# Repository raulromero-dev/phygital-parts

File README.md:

# Phygital Parts

Live at [phygitalstudio.app](https://phygitalstudio.app/).

A standalone hardware workbench for discovering components, visualizing their
fit, planning real cables, and deciding what to buy. Start with a description,
a reference photo plus a prompt, or public links to a project or product.

The homepage offers six **prebuilt starters** without an API key: makeup cyberdeck,
thermal camera, air monitor, wearable haptics, smartwatch and smart ring.
Each opens a populated 3D layout with proposed connections, sourcing links
and review notes. Original Phygital compact, bench and wide layouts remain
available through their direct project URLs.

Each starter has its own URL and browser-storage namespace:
`/examples/thermal-camera`, `/examples/air-monitor`, `/examples/wearable-haptics`,
`/examples/smartwatch`, `/examples/smart-ring`, `/examples/makeup-cyberdeck`, and
`/projects/phygital?layout=compact` (also `bench` or `wide`). Autosaves,
snapshots and chat histories stay separate. The Phygital route retains the
original project inventory, notes and source context, with links to its firmware
repository and original workbench. Existing root-page projects remain available.

### Saving and returning

**My projects** lists account projects and older browser saves. Sign in with
Google to return from any device. New prompted builds save to your account while
signed in. Use **Projects → Save to account** to copy an existing browser project;
its original stays local. Account edits and the last 40 chat messages autosave.

Without sign-in, projects remain in this browser. **Save a copy** and **Import
project** create independent projects; they never replace the source. Copies and
imports go to your account when signed in. The sidebar name is editable, and
named layouts keep independent parts, placements and cables within one project.
Use the layout selector and compare button to switch, duplicate, rename or remove
alternatives. They autosave to the account or browser with the project; older
snapshots remain available under **Layouts → Older snapshots & examples**.

**Export → Project file** creates a portable JSON backup of the assembly, cables,
custom parts, all layout alternatives, notes and decisions (no chat or keys). Clearing site data removes
browser copies, not account copies. A cloud URL requires its owner's sign-in;
it does not make the project public. Save failures and conflicts are visible;
conflicts preserve your draft and offer Save a copy instead of overwriting.

See [account setup](docs/ACCOUNTS.md) to configure a fork and run database checks.

The smart ring reuses SenseRing's four original CAD meshes: sensor board,
curved battery, inner shell and outer shell. It is a custom fabrication reference,
not a plug-in kit. Battery availability and curved clearances need review.
Editable CAD, PCB files, source meshes, conversion script and GPL-3.0 license
are available at `/reference/sense-ring/source.zip`.

The smartwatch uses a Seeed
XIAO ESP32-S3, Round Display, included antenna allowance and LiPol LPR553535
round 600 mAh battery candidate. It maps the 14 direct header contacts and antenna coax.
The battery remains unconnected: its 300 mA charge limit is below the board’s
approximately 485 mA setting, and its PHR-2 plug requires an adapter. LiPol lists
a five-piece minimum for stocked samples; confirm availability and pricing. Published
PCB data and the existing XIAO CAD are reused; thickness, antenna geometry and
the proposed enclosure are estimates. Inspect each part for manufacturer purchase links and pinouts; the project
includes open-source examples and a printable case reference.

This repository is independent of the original Phygital sensor firmware. It
contains the product experience and a reusable reference-model library, not the
surveillance device's firmware or detection rules.

The makeup cyberdeck pairs M5Stack's current Cardputer-Adv with an original
blush compact cradle, hinged lid and mirror insert. Manufacturer STL is reused
under MIT; the case is an open-position fit concept. Hinge collisions remain
visible for review. The controller, keyboard, screen and 1500 mAh battery are
integrated, so the starter has no external conductors. See **Pins & internals**
for the internal map and Grove expansion contacts. Source and license bundle:
`/reference/makeup-cyberdeck/source.zip`.

Select a component and ask Codex, for example: “Find an alternative near 02134
from Amazon or Micro Center that I can get within two days.” You can also use
Find parts → codex. Include a city/ZIP and deadline; no precise address is needed.
Codex can search the web, compare the exact SKU and connection requirements, and
show retailer links with dated availability evidence. Generic stock is kept
separate from arrival dates. Missing evidence stays unverified; results older
than a day ask you to recheck. **Check fit & add…** researches a candidate for
review; it never automatically swaps your existing component or purchases it.
Shopping cards stay in private account/browser chat, excluded from shared layouts.

Find parts cards show names, dimensions and purchasing actions first. Interface
text and research descriptions are available in collapsed details. Research
and link forms use brief labels instead of introductory subtitles. The homepage
accepts part links directly in the main prompt, without a separate links field.
A first prompt opens its own project URL with the floating Codex window open.
Validated draft parts appear progressively, followed by source CAD or an
image-derived model. Codex shows real progress, elapsed time and Stop.
Canceled or interrupted builds retain their draft parts.
Stages come from provider events; no percentage is invented. Loading shows quiet
action text. The optional Cable Hop game opens from Codex while work continues
in the background.

## For agents and contributors

Start with [AGENTS.md](AGENTS.md), [architecture](docs/ARCHITECTURE.md),
[adding parts](docs/ADDING_PARTS.md), and [CONTRIBUTING.md](CONTRIBUTING.md).
These explain the product context, model provenance, coordinates, connection
rules, code boundaries, local setup and validation workflows.

The reusable [Phygital skill](skills/phygital/SKILL.md) helps agents discover parts,
compare fit and plan connections. Its name and description support automatic
skill discovery; invoke it explicitly as **`$phygital`**. Install from a checkout:

```sh
mkdir -p ~/.codex/skills
cp -R skills/phygital ~/.codex/skills/
```

Start a new Codex session to refresh skill discovery. The same package is available
as [a downloadable skill](https://phygitalstudio.app/skills/phygital.zip) or
[readable instructions](https://phygitalstudio.app/skills/phygital.md). Other agents
can load `SKILL.md` with their own skill mechanism. To update the distribution
from source, run `npm run skill:package` (Python 3). This is a repository-distributed
skill; it does not require a hosted tool server.

Original application code, documentation and the skill are MIT licensed.
Third-party CAD, derived assets, fonts and icons retain their existing attribution
and terms; the application license does not relicense those files.

## Use

1. Describe a project on the homepage, or choose a prebuilt starter.
2. Connect your own OpenAI API key to use **GPT-6 Astra**. Research uses the
   Responses API, image input, web search and structured output.
3. Review the proposed parts, sources, unknowns and conductors. Select the parts
   to add. An AI response never silently replaces the current assembly.
4. Use **Find parts** to search the local library, work with codex, paste a product URL,
   or add a component manually. Purchase links are prominent on cards and in
   the part inspector. Search-result links are labeled as searches; stock and
   prices are not promised.
5. Arrange parts in 3D, adjust dimensions, set enclosure bounds, inspect fit
   checks, and map individual contacts in **Connections**. Export JSON to move a
   project between browsers, GLB for Blender, or CSV for the cable plan.
6. Open **codex** for a floating, expandable chat. Select a part to attach
   its context, then request movement, rotation, corrected dimensions, enclosure
   changes or review notes. Review each proposal and choose **Apply changes**;
   the edit is undoable. Proposals are rejected if the assembly has changed
   since the request. Codex can also add or duplicate catalog/existing parts and
   map their contacts. Ask for alternatives to receive up to four independent
   layout proposals at once. **Save layouts** keeps the original active; use
   **Compare layouts** to open an option. A project holds up to eight layouts.

The interface supports light/dark mode and Color/Mono component rendering.
An outline board logo, a one-turn entrance animation and very faint circuit
traces decorate the homepage in both themes; reduced-motion preferences disable
animations. Controls use modestly rounded corners. On mobile, a compact project
menu groups key connection, theme, layouts and export.
Custom builds require a typed description; there is no Start empty shortcut.
All starters load locally without an AI call. The air monitor reuses
Sensirion sensor CAD and Seeed PCB data; its USB-C supply, firmware, ventilation
and peak-current budget need review. Haptics use four separate multiplexer
channels with the existing power-budget checks.
Known exact parts reuse the existing CAD/model library. Other parts first try
source GLB, STL or STEP (up to 2.8 MB); otherwise Astra reads a product image
and creates a bounded visual approximation. Missing sources keep
clearly labeled, dimensioned parametric envelopes. Research suggestions and pinouts need review.

## Local development

Node 22+ and npm are recommended.

```sh
npm ci
npm run dev
```

Open the printed local URL (default `http://127.0.0.1:5179`). The local server
runs Vite and the same `/api/research`, `/api/adjust`, `/api/model` and `/api/assets` handlers used in production.
`npm run dev:ui` is frontend-only; use the normal dev command to exercise either API.

```sh
npm test
npm run build
```

## API keys and data

- Each visitor brings their own OpenAI API key. There is no owner-funded key or
  shared spending pool. OpenAI bills the visitor's API project.
- Keys remain in JavaScript memory for that tab. They are not stored in
  localStorage, project files, snapshots, URLs, analytics or application logs.
  Reload or **Disconnect** removes the in-memory key.
- A research or adjustment request sends the key over HTTPS to this app's server, which relays
  it only to `https://api.openai.com/v1/responses`. This is a server-mediated
  integration, not a claim that the app server never sees the key.
- Prompts, supplied links, the chosen image and relevant assembly details are
  sent to OpenAI when research is requested. Adjustments send assembly details,
  selected-part context and the last eight chat messages. Requests set `store: false`; this
  does not override OpenAI's account-level retention or abuse-monitoring policy.
- Browser projects and their last 40 chat messages stay local. Account projects
  and chat sync to Supabase under the signed-in owner, with account-scoped local backups. Pending proposals are not restored
  after reload. Chat history is anchored above the composer with newest messages
  at the bottom. Images and credentials are not saved in projects or chat history.
- Supports one PNG/JPG/WebP up to 2 MB, five public links, 20 returned parts,
  60 assembled parts and 40 custom parts. Research has a 240-second upstream
  timeout, bounded model output/tool calls, and cancellation in the UI.
- The server never fetches arbitrary supplied URLs itself. OpenAI's web search
  reads public sources; private repositories and login-only pages are not
  automatically accessible. Errors, refusal and incomplete output never add parts.

## Analytics

Vercel Web Analytics is enabled for the hosted project. Production builds use
`@vercel/analytics` for standard page views; development builds do not inject it.
No custom events include prompts, project contents, images, keys or chat messages.
Forks must enable Web Analytics in their own Vercel project before deploying.

## Deployment

The Vercel project is `phygital-parts`, separate from the original studio.

```sh
vercel link # select your own project when deploying a fork
vercel deploy --prod
```

Vercel builds `dist/` and deploys the `api/` handlers as Node functions. No API key
or database environment variable is required. Function duration is configured
for up to 300 seconds; the hosting plan must support it. Public access is an
intentional product setting. Custom domain registration and payments are not
part of this repository.

## Structure

- `src/product.js`, `product.css`: prompt-first home, key connection, finder,
  progressive project builds and reviewed part additions.
- `src/product-data.js`: safe supplier links, blank projects, duplicate parts,
  placement suggestions and applying research proposals.
- `src/main.js`: workspace, component inspector, wiring editor, notes and export.
- `src/routes.js`, `templates.js`: isolated starter URLs and prebuilt assemblies.
- `src/assistant.js`, `adjustments.js`: floating chat, part context, local history
  and reviewed, undoable part additions/removals, cable maps and placement proposals.
  Questions show selectable answers plus Other; answers preserve selected-part context.
- `src/viewer.js`, `proxy.js`: Three.js scene, source model reuse and approximate
  geometry for custom components.
- `src/engine.js`, `connections.js`: fit checks, project validation and pin maps.
- `server/research.mjs`, `schema.mjs`: GPT-6 Astra request, input limits, structured
  output validation and safe error handling.
- `server/adjust.mjs`: bounded assembly context and structured adjustment output.
- `public/models/`: reusable GLBs. `blender/vendor/README.md` and source manifests
  document manufacturer geometry, attribution, licenses and approximations.
- `tests/`: fit/wiring regression tests and API/project-data integration tests.

## Verification and limits

Tests cover fit and wiring regressions, generic empty projects, duplicate CAD
reuse, source/contact persistence, malicious imports, request limits, image/link
input, refusal, upstream errors, and a mocked successful Responses result.
Browser checks cover the homepage, generic finder, purchase actions, custom
parts, settings and persistence. The test suite also covers separate routes,
original Phygital geometry, ring CAD assembly, adjustment validation and linked
carrier movement. A local mock provider verified chat review, apply and undo;
mobile checks cover the compact menu and expanded chat bounds. A successful paid GPT-6 Astra response requires
a visitor key with model access and credits; no owner credential is bundled.

Bounding-envelope collision checks are planning aids. They do not prove cable
bend radius, connector mating, electrical safety, firmware compatibility,
thermal performance, or manufacturability. Exact CAD revision, source dimensions
and delivered hardware must be checked before purchase and assembly.

## Model provenance

Third-party models, fonts, photographs and source CAD retain their original
licenses and authorship. See `blender/vendor/README.md`, the vendor `sources.json`
files, image `.source.json` files and `public/fonts/*LICENSE.txt`. This repository
does not relicense manufacturer assets or claim vendor endorsement. Blender
source scripts and vendor files are retained; binary working `.blend` files and
the original user's bench photograph are not copied into this product.

OpenAI implementation references:
- https://developers.openai.com/api/docs/models/gpt-6-astra
- https://developers.openai.com/api/docs/guides/tools-web-search
- https://developers.openai.com/api/docs/guides/structured-outputs

### Progressive models

New projects use `/projects/build-<uuid>` with a separate browser autosave and
chat history. The URL identifies local browser data; it is not a hosted share
link. Reload preserves drafts but does not resume paid requests. Keys and
uploaded reference images remain in tab memory.

Research discovers exact CAD downloads and reference images with source pages.
`/api/assets` downloads public HTTPS assets with pinned public IPv4 DNS, redirect,
time and size limits. GLB previews reject external resources; STEP triangulation
runs in a time-limited worker using occt-import-js. CAD proportions are preserved
with uniform scaling to the research envelope; orientation and dimensions still
need verification. Images go to Astra through `/api/model` and return up to 128
bounded primitives, never executable code. Model requests use the visitor key,
can incur additional API charges, and run at most two at a time.

Each component retains its model evidence under **Source & evidence**. Missing,
large or unsupported CAD can fall back to image reconstruction or a labeled
envelope. This flow does not filter source CAD by redistribution-license status.
OpenCascade runtime notices are in `public/third-party/`.

### Cable Hop

Codex progress uses text describing real research and modelling actions. The
optional **Cable Hop** button in the Codex header (also available during builds)
opens a separate 3D minigame. Tap or press Space to lift a four-wire connector,
clear six header gaps and dock into a chip. P pauses; Escape closes. Builds
continue in the background. The game needs no key or AI requests, keeps
only the best local score, pauses when hidden, and disposes its graphics on close.
The blue PCB, connector, metal pins and wire models are original game art.

### Share a project

Choose **Share → Create share link**. Visitors can explore the layout and cable
mapping without signing in. **Remix** creates a separate project in their own
Google account. Update the published version or turn the link off from Share.
Chat, prompts and private project notes are excluded. See [account and sharing
setup](docs/ACCOUNTS.md) for the database contract.

### Preview screen firmware

**Simulate** lives beside Layout and Connections. Try the actual Phygital/Haldzemo
screen renderer, switch test scenes, tap its controls and adjust synthetic inputs.
Choose **Download files** for the preview, current test settings, layout/wiring,
screen PNG and matching editable renderer source. **Save preview to project**
also keeps scene, input values and pause state. Other projects can import a
compiled preview built from their own firmware using the
[framebuffer adapter guide](docs/FIRMWARE_PREVIEWS.md). This previews screen behavior;
it does not emulate the full ESP32 or validate wiring.

Codex chat also accepts photos through the **＋** attachment button, clipboard
paste or drag-and-drop. Up to four JPG/PNG/WebP photos are resized before sending
to the visitor's AI provider. Photos remain in tab memory; saved chat retains
attachment counts, and asks you to reattach after a reload.

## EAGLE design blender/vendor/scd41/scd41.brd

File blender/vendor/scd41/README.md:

# Seeed Grove SCD41 reference geometry

Retrieved 2026-11-14 from the [Seeed SCD41 documentation](https://wiki.seeedstudio.com/Grove-CO2_&_Temperature_&_Humidity_Sensor-SCD41/):

- [Sensirion SCD4x STEP](https://files.seeedstudio.com/wiki/Grove-CO2%26Temperature%26HumiditySensor-SCD4/res/Sensirion_CO2_Sensors_SCD4x_STEP_file.step), retained unmodified as `scd4x.step`.
- [Seeed board archive](https://files.seeedstudio.com/wiki/Grove-CO2%26Temperature%26HumiditySensor-SCD4/res/SCH%26PCB.zip), unmodified v1.01 Eagle board and schematic extracted as `scd41.brd` and `scd41.sch`.
- [Product / purchase page](https://www.seeedstudio.com/Grove-CO2-Temperature-Humidity-Sensor-SCD41-p-5025.html).

Manufacturer files remain attributed to Seeed / Sensirion under their original terms. The Eagle board carries its Creative Commons / OSHW notices; no additional rights are asserted over vendor CAD.

The planning GLB reuses the SCD4x sensor mesh and the Eagle `BORDER_1U-DIM-W/-DRILL` outline (20 × 24.2 mm including tabs). The Grove connector body and component heights are approximations. A 14 mm overall height is a planning allowance. J1 nets come directly from the board: 1 SCL, 2 SDA, 3 VCC, 4 GND. The chip package is labeled SCD40-D-R2 in the manufacturer's SCD41 board; the vendor SCD4x family CAD is reused as supplied.

Regenerate:

```sh
node blender/convert-cad.cjs scd4x
/Applications/Blender.app/Contents/MacOS/Blender --background --python blender/air-monitor.py
```

The example proposes 3.3 V operation within Seeed's 2.4–5 V range and I²C address 0x62. The carrier regulator's peak-current capacity, temperature compensation, ventilation and firmware still need review. No stock, pricing, calibrated performance or finished device is promised.

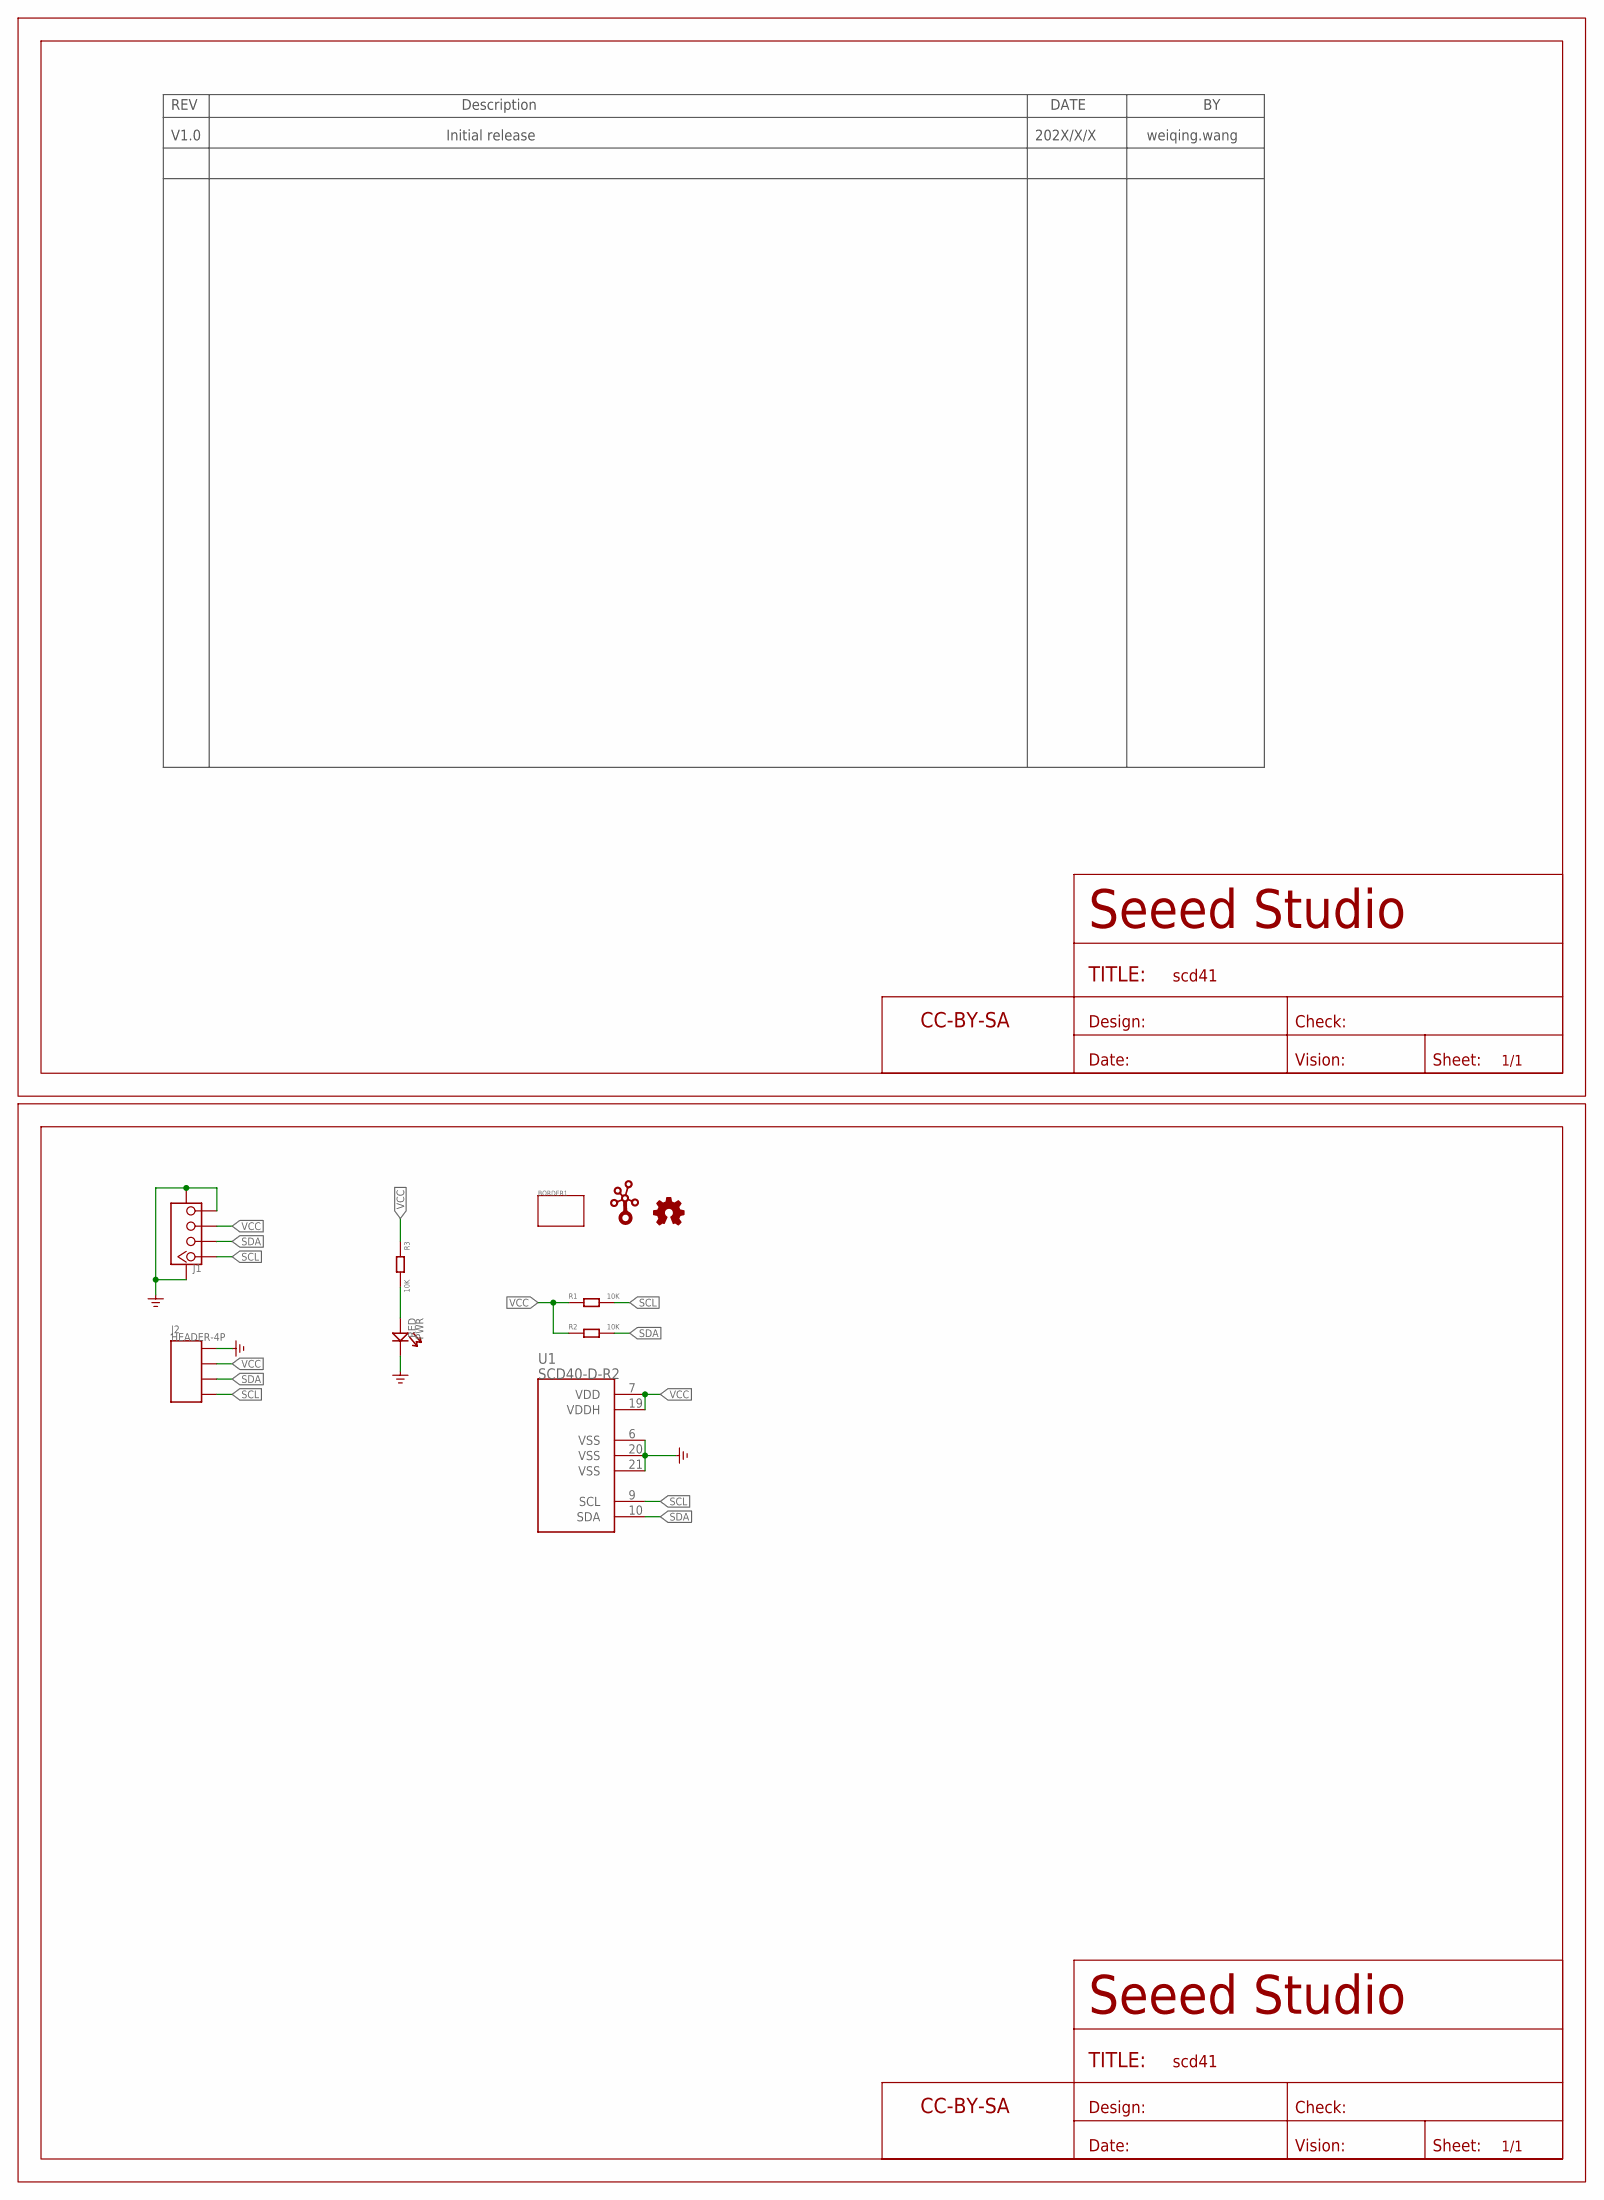
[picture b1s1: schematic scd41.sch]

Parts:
BORDER1: BORDER_TWIG1U; BORDER_1U-DIM-W/-DRILL
FRAME1, FRAME2: FRAME; CREATIVECOMMONS
J1: GROVE_4P-2.0\SMD\FEMALE-HORIZONTAL; GROVE_4P-2.0\SMD\HOR
J2: HEADER-4P
LOGO1: LOGO_GROVETWIGLOGO_SMALL; LOGO_GROVE-SILK-SMALL
LOGO2: LOGO_OSHWX0100-NT; LOGO_OSHW_FILLX100_NOTEXT
PWR: RED; LED-0603
R1, R2, R3: 10K; R0603_NORMAL
U1: SCD40-D-R2

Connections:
GND: J1.4, J1.SS1, J1.SS2, J2.P$1 (1), PWR.-, U1.6 (VSS), U1.20 (VSS), U1.21 (VSS)
unnamed: PWR.+, R3.2
SCL: J1.1, J2.P$4 (4), R1.2, U1.9 (SCL)
SDA: J1.2, J2.P$3 (3), R2.2, U1.10 (SDA)
VCC: J1.3, J2.P$2 (2), R1.1, R2.1, R3.1, U1.7 (VDD), U1.19 (VDDH)

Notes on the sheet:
Initial release
V1.0
202X/X/X
weiqing.wang

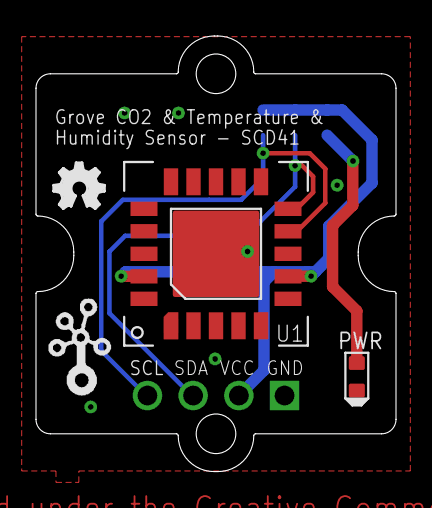
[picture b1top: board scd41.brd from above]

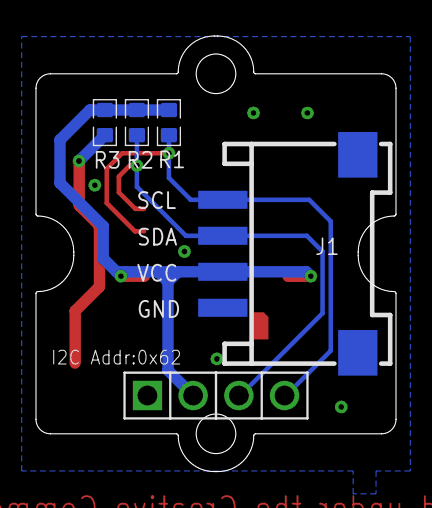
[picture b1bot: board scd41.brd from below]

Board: 2 copper layers, 20.0 x 24.2 mm, 12 parts (4 on the bottom side), 5 nets.

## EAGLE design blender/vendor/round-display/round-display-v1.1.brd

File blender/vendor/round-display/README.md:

# Seeed Round Display for XIAO v1.1

Original Eagle board, downloaded 2026-11-14 from Seeed's published design archive:
https://files.seeedstudio.com/wiki/round_display_for_xiao/SeeedStudio_Round_Display_for_XIAO_v1.1_SCH&PCB_230407.zip

Manufacturer documentation and attribution:
https://wiki.seeedstudio.com/get_start_round_display/
https://wiki.seeedstudio.com/seeedstudio_round_display_usage/

`blender/smartwatch.py` reuses the curved PCB outline, component placement centres,
J4/J5 socket centres and contact spacing. Glass, passive bodies, connectors and
all component heights are approximate; the dial is illustrative. Published
specifications disagree on 39 mm vs 43 mm: the product page gives 43 mm, while
the wiki describes the 39 mm glass. The app uses a 43 × 43 × 10 mm planning envelope.

The XIAO model reuses the existing Seeed manufacturer STEP-derived GLB. The antenna reuses an existing planning mesh, with qualified dimensions.
The round battery uses `blender/round-battery.py`, based on the drawing below.
The battery is not wired: its PHR-2 connector needs a verified adapter to J1,
and its 300 mA maximum charge current is below the board’s listed 485 mA.

Manufacturer printable case reference (linked, not represented as a validated fit):
https://files.seeedstudio.com/wiki/round_display_for_xiao/Round-Display-shell-3D-Model.stl

Open-source Arduino examples (MIT; linked, not bundled):
https://github.com/Seeed-Studio/Seeed_Arduino_RoundDisplay

Round battery source, checked 2026-11-14:
https://www.lithium-polymer-battery.net/iec62133-certified-lpr553535-3-7v-600mah-2-22wh-round-lithium-polymer-battery-with-pcm-wires-jst-phr-2/
https://www.lithium-polymer-battery.net/wp-content/uploads/2024/02/LPR553535-600mAh.pdf

Drawing specifies a 35 mm diameter body with one flat edge, 32 mm overall body
depth and 5.5 mm maximum thickness; 50 ± 3 mm leads and the PHR-2 plug need
additional space. The mesh omits free leads and plug; PCM, foil and tape are
illustrative. Standard charging is 120 mA, maximum 300 mA. The original Adafruit
part remains in the library to preserve saved or imported user-edited projects.

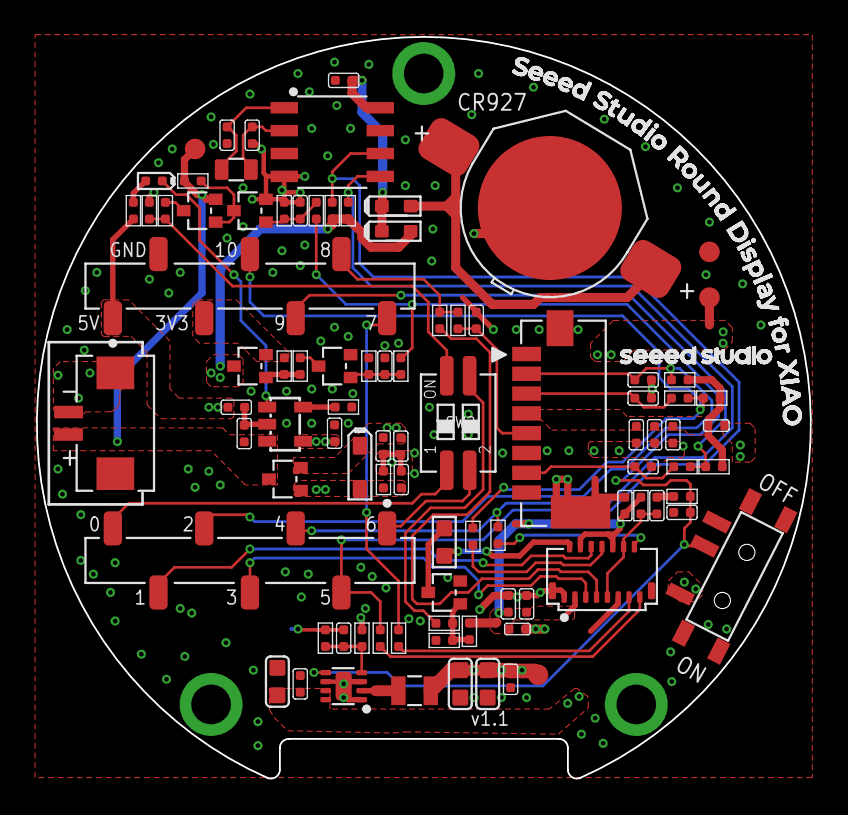
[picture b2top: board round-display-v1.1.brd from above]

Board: 2 copper layers, 43.0 x 41.2 mm, 99 parts (0 on the bottom side), 49 nets.

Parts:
BAT1: CR927; BAT2P-SMD-15.3X8.6X2.9MM
C1, C2, C5, C13: 4.7uF; C0402
C3, C8, C9, C12, C16, C18, C19, C20, C21: 100nF; C0402
C7, C10, C11: 10uF; C0603
C14, C25: DNP; C0402
C15: 18pF; C0402
C17: 10uF; C0402
C22, C24: 100pF; C0402
C23: 1uF; C0402
D1: RED; LED-0402
D2: B5819WS; SOD-323
D3: ESD9B3.3ST5G; ESD-0402
D4, D5: 1N4148WT; SOD-523
D6, D7, D8, D9, D10: ESDPSA0402V05; ESD-0402
FB1, FB2: 120R/2A; F0402
FR1, FR2, FR3, FR4: SEEEDSTUDIO-OPEN-SCH-FRAME; SEEEDSTUDIO-PCB-FRAME
J1: BAT; HW2+2P-SMD-1.25
J2: ST-TF-003D-3-2; MICRO-SD8+2P-SMD-1.1-11.41X4.9X3MM
J4, J5: ST-FH-254-0114; H7-2.54-18.28X2.5X5MM
J6, J7, J8: H1P-3.5/2.2MM-PASTE
J9: FPC15P-0.6-6.1X2.83X1MM
L2: 1uH; L201610
Q1, Q2, Q5: CJ3134KW; SOT-323
Q3, Q4, Q6: CJ2101; SOT-323
R1, R7, R13, R21, R26: 470K; R0402
R2: 2.4K; R0402
R3, R8, R18: 100K; R0402
R5: 5.1K; R0402
R6: 2K; R0402
R9, R22, R23, R24, R25, R32: 0R; R0402
R10, R11, R12, R20, R30, R31: 4.7K; R0402
R14, R15, R16: 33R; R0402
R17: 10R; R0603
R19: 1K; R0402
R27: 10K; R0402
R28, R29: 470K 1%; R0402
R33: DNP; R0402
R34: 22K; R0402
SW1: DHT-1200S; SW7-SMD-6.7X2.6X1.4MM-90D
SW2: 311080226; SW4-SMD-1.27-5.4X4.14X2.3MM
TP1, TP2, TP4, TP6: TP-D45MIL
U1: ETA3410; DFN8G-0.5-2X2MM
U2: ETA4054S2F; SOT-25
U4: PCF8563; SOP8-1.27-5X3.9MM
U$1: LOGO-SEEED-NEW-0.94X8.4MM
X1: 32.768KHz/306010020; X2-SMD-L2.0X1.2X0.55MM

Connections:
A0/BAT: J5.7, SW2.1
BAT_READ: R28.1, R29.2, SW2.4
BG_LIGHT: R19.1, SW2.3
D1/LCD_CS: J5.6, J9.6
D2/SD_CS: D6.2, J2.P2, J5.5, R12.1
D3/LCD_DC: J5.4, J9.5
D4/SDA: J5.3, R25.1, R30.1, U4.5
D5/SCL: J5.2, R24.1, R31.1, U4.6
D6/TX: J5.1, SW2.2
D7/TP_INT: J4.7, R32.1
D8/SCK: J4.6, R15.2, R22.1
D9/MISO: J4.5, R10.1, R14.2
D10/MOSI: J4.4, R11.1, R16.2, R23.1
GND: BAT1.3-, C1.1, C2.1, C3.1, C5.1, C7.1, C8.1, C9.1, C10.1, C11.1, C12.1, C13.1, C14.1, C15.2, C16.2, C17.1, C18.1, C19.1, C20.1, C21.1, C22.1, C23.1, C24.1, D3.1, D6.1, D7.1, D8.1, D9.1, D10.1, J1.2, J1.P1, J1.P2, J2.P6, J2.S1, J2.S2, J4.2, J6.1, J7.1, J8.1, J9.1, J9.11, J9.16, J9.17, Q1.2, Q2.2, Q5.2, R1.1, R2.1, R3.1, R21.1, R26.1, R29.1, R33.1, R34.1, SW1.P1, SW1.P2, SW1.P3, SW1.P4, TP4.T, U1.1, U1.3, U1.6, U1.9, U2.2, U4.4
LCD_3V3: C17.2, C18.2, C20.2, FB2.2, J9.3, J9.4, J9.10, R18.2, R27.2
LCD_RST: C19.2, J9.9, J9.12, R27.1
LEDK: J9.2, R17.2
unnamed: R2.2, U2.5
unnamed: J9.13, R32.2
unnamed: D1.+, R6.1
unnamed: C25.1, R8.1, R34.2, U1.4
unnamed: D1.-, U2.1
unnamed: Q4.3, R28.2
unnamed: C23.2, Q2.1, R5.2, R21.2
unnamed: L2.1, U1.2
unnamed: Q4.1, Q5.3, R7.1
unnamed: Q3.1, R9.2, R13.1
unnamed: C14.2, U4.2, X1.1
unnamed: Q2.3, R9.1
unnamed: D8.2, J2.P7, R14.1
unnamed: D9.2, J2.P5, R15.1
unnamed: D10.2, J2.P3, R16.1
unnamed: C15.1, U4.1, X1.2
unnamed: Q1.1, R18.1, R19.2, R33.2
unnamed: J9.7, R22.2
unnamed: Q1.3, R17.1
unnamed: C16.1, D4.-, D5.-, U4.8
unnamed: J9.8, R23.2
unnamed: BAT1.1+, BAT1.2+, D5.+
unnamed: C24.2, Q5.1, R20.2, R26.2
unnamed: J9.14, R25.2
unnamed: J9.15, R24.2
PWR_EN: C22.2, R1.2, R5.1, R20.1, SW1.2, U1.5
SYS_3V3: C10.2, C11.2, C21.2, C25.2, D4.+, FB1.1, FB2.1, L2.2, Q3.3, R8.2, R30.2, R31.2, TP6.T
USB_5V: C1.2, C3.2, D2.+, D7.2, J4.1, Q6.1, R3.2, R6.2, U2.4
VBAT: C5.2, J1.1, Q4.2, Q6.3, R7.2, TP1.T, U2.3
VDD_3V3_SD: C12.2, C13.2, D3.2, FB1.2, J2.P4, R10.2, R11.2, R12.2
VSYS: C2.2, C7.2, C8.2, C9.2, D2.-, Q6.2, SW1.1, TP2.T, U1.7, U1.8
XIAO_3V3: J4.3, Q3.2, R13.2

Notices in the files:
parts and their libraries:
moudle-new: This work is licensed under the Creative Commons Attribution 4.0 International License.
To view a copy of this license,visit:
http://creativecommons.org/licenses/by-sa/4.0
Seeed-OTHER: CC-BY-SA
